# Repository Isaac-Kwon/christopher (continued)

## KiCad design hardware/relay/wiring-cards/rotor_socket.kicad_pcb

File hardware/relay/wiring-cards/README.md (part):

# 릴레이 배선 카드: 로터 카드 W와 반사판 카드 U (Phase 3 R 트랙, 회로도 + 기판 배치)

작성일: 2026-11-15 (8절 카트리지 방식 2026-11-16) · 상태: **회로도(KiCad 10) 생성·ERC 0건, 유닛 전체 넷리스트 합성·시뮬레이션·음성 시험 통과, 기판 배치(배선 없음) DRC 0건. 관람객용 카트리지 방식(받침 기판 + 카트리지 8종)도 같은 단계** · 관련: `hardware/relay/layout.md` 3.2·3.4절(카드 순서와 점퍼), `hardware/relay/concept.md`, `hardware/relay/shifter-board/README.md`(틀과 J1–J4 자리), `docs/decisions/0003-interfaces.md`(26선 D-sub, 27–29번, `CHASSIS`), 기준 모델 `crates/christopher-core/src/relay.rs`

**표기.** **(계산)** = 이 문서의 산술, **(추정)** = 시제품 전 값. 단위 mm.

## 1. 무엇인가

릴레이 유닛(`S(a1) W_R S(a2) W_M S(a3) W_L S(−l) + 반사판 + 같은 보드를 거꾸로`)에서 시프터가 아닌 **수동 배선 카드** 두 종류.

| 카드 | 종류 | 내용 | 프로젝트 |
|---|---|---|---|
| **W** (로터) | 8종 (로터 I–VIII 하나씩) | 가는 길 `i → W[i]`, 오는 길 `W[i] → i` (= W⁻¹). 커넥터 4개(J1–J4), 부품은 커넥터와 장착 구멍뿐 | `rotor_I` … `rotor_VIII` |
| **U** (반사판) | 2종 (B, C. 얇은 반사판은 불필요) | 가는 길 `i → R[i]`로 되돌림. 커넥터 2개(J2, J3) | `reflector_B`, `reflector_C` |

배선은 `data/wirings/enigma.txt`에서 생성한다(단일 출처). 카드는 **시프터와 같은 외곽 250 × 228, 같은 구멍 4개, 같은 D-sub 37 풋프린트를 시프터의 J1–J4와 같은 좌표·방향에** 둔다. 층은 2층(수동이라 충분, 4층으로 바꿔도 배치는 같다).

| 파일 | 내용 |
|---|---|
| `gen_cards.py` | 열 개 프로젝트(`.kicad_pro`, `.kicad_sch`)를 생성. 회로도는 평면 한 장(A3) |
| `gen_cards_pcb.py` | 기판 배치 생성(외곽, 구멍, 커넥터, 넷리스트, 실크). 배선 없음 |
| `verify_cards.py` | **유닛 전체 넷리스트 합성 + 스크램블러와의 비교 + 음성 시험**(4절) |
| `verify_cards_pcb.py` | 배치 대 회로도, DRC, 시프터와 같은 자리, 결정성, 음성 시험(5절) |
| `ki_common.py` | KiCad 보조 모듈. `hardware/gear/contact-board/ki_common.py`와 **같은 사본** |

생성물은 UUID를 고정해 두어 다시 생성해도 바이트 단위로 같다. 손으로 고치지 말고 생성기를 고친다.

## 2. 규약: 쌓기의 방향 (명시)

**커넥터 이름은 시프터의 J1–J4 자리 이름이고 신호의 방향이 아니다.** 시프터는 J1(가는 길 입력)·J2(오는 길 입력)가 한 변, J3(가는 길 출력)·J4(오는 길 출력)가 맞은편 변이다. 로터 카드와 반사판 카드는 같은 자리에 같은 이름을 쓰되 기능이 다르다.

| 카드 | 커넥터 (자리) | 기능 | 쌓기에서의 변·자리 |
|---|---|---|---|
| W | **J3** (오른쪽 변 h1) | `OUTBOUND_IN` 가는 길 입력 | 아래 h1 |
| W | **J4** (오른쪽 변 h2) | `RETURN_IN` 오는 길 입력 | 아래 h2 |
| W | **J1** (왼쪽 변 h1) | `OUTBOUND_OUT` 가는 길 출력 | 위 h1 |
| W | **J2** (왼쪽 변 h2) | `RETURN_OUT` 오는 길 출력 | 위 h2 |
| U | **J3** | `OUTBOUND_IN` (S4의 가는 길 출구에서 받음) | 아래 h1 |
| U | **J2** | `RETURN_OUT` (S4의 오는 길 입구로 보냄) | 위 h2 |

- **왜 W의 입력이 J3·J4인가.** layout.md 3.2절: S1–S3와 W와 U는 부품면이 **뒤**를 보고, 연결 변이 위와 아래다. 뒤를 보는 카드는 J3·J4 변이 **아래**, J1·J2 변이 **위**다(시프터 S1–S3 표). 신호는 S1에서 S4 쪽으로 가므로 W의 입력은 앞 시프터 S(k)의 **출력 변(J3·J4, 아래)**에서 받고, 출력은 다음 시프터의 **입력 변(J1·J2, 위)**으로 나간다. 그래서 W 입력이 J3·J4(아래), 출력이 J1·J2(위)다. 결과로 **같은 자리의 커넥터끼리 곧게 잇는** 규칙(`S1.J3 – W_R.J3`, `W_R.J1 – S2.J1`, …)이 성립한다.
- **a4(앞을 보는 S4)**는 J1·J2가 아래, J3·J4가 위다. S4는 시프터 기판의 **S4 변형**(`shifter_board_s4.kicad_pcb`, 7절 1번)이다: 신호 배정과 변·자리는 표준과 같고 J1–J4가 뒷면에 거울로 놓여 점퍼 14가닥 모두 양 끝 소켓의 핀 1이 같은 끝에 온다. 가는 길은 위의 J3으로 들어가 아래의 J1로 나온다(`−l`).
- 카드가 쌓기에서 도는 방식(앞 보기/뒤 보기, 변과 자리)은 `verify_cards.py`의 `POSE` 표에 있고, **점퍼 14가닥은 이 표에서 도출한다**: 변·자리마다 앞에서 뒤 순서로 커넥터를 두 개씩 짝지으면 layout.md 3.4절의 표와 정확히 같다(길이 39 ×2, 64 ×2, 25 ×10도 같음). 짝이 없는 끝이 `IN`(S1.J1)·`OUT`(S1.J4) 리드다.

점퍼(핀 n = 핀 n, 37선 1:1):

| 변·자리 | 점퍼 |
|---|---|
| 아래 h1 | S4.J1 – U.J3 · W_L.J3 – S3.J3 · W_M.J3 – S2.J3 · W_R.J3 – S1.J3 |
| 아래 h2 | S4.J2 – W_L.J4 · S3.J4 – W_M.J4 · S2.J4 – W_R.J4 · S1.J4 → `OUT` 리드 |
| 위 h1 | S4.J3 – W_L.J1 · S3.J1 – W_M.J1 · S2.J1 – W_R.J1 · `IN` 리드 → S1.J1 |
| 위 h2 | S4.J4 – U.J2 · W_L.J2 – S3.J2 · W_M.J2 – S2.J2 · W_R.J2 – S1.J2 |

전류의 길: `IN` → S1 → **W_R(J3→J1)** → S2 → W_M → S3 → W_L → S4(J3→J1) → **U(J3→J2)** → S4(J4→J2) → **W_L(J4→J2)** → S3 → W_M → S2 → W_R → S1 → `OUT`.

## 3. 카드의 회로

**W 카드 (로터 N).** 핀 1–26 = 선 A–Z. 가는 길: **J3 핀 i+1 → J1 핀 W[i]+1** (네트 `OW_<입력><출력>`, 예: 로터 I `OW_AE`). 오는 길: **J4 핀 j+1 → J2 핀 W⁻¹[j]+1** (네트 `RW_<입력><출력>`). 즉 오는 길은 같은 와이어링을 거꾸로 읽는다(`relay.rs`의 `backward`). 로터 한 장에 2-핀 네트 52개. W[i]는 enigma.txt의 "입구쪽 → 반사판쪽" 표(코어 오프셋 0)이고, 로터의 회전은 시프터 쪽(`a1…a4`)이 한다. 카드에는 이동 위치·노치가 없다.

**U 카드 (반사판 N).** **J3 핀 i+1 ↔ J2 핀 R[i]+1** (네트 `RF_<입력><출력>`, 26개). 반사판은 고정점 없는 대합(R[R[i]] = i)이므로 카드를 끝에서 끝으로 돌려 꽂아도(J3↔J2) 같은 배선이다(7절 2번).

**공통.** 핀 27–29(0 V 기준선, 0003 5.2절)와 30–37은 어디에도 잇지 않는다(`no_connect`, 점퍼의 27–37 가닥은 양쪽 모두 떠 있다). D-sub 껍데기(풋프린트 패드 `SH`, 커넥터마다 2개)와 장착 구멍 H1–H4(도금 M3)는 `CHASSIS`(0003 7.1절). 이 카드에는 0 V도 전원도 없으므로 `CHASSIS`–0 V의 R6·C1은 시프터에만 있다(`CHASSIS` 넷에 PWR_FLAG 하나, ERC용).

## 4. 유닛 전체 검증 (`verify_cards.py`)

`python verify_cards.py [--samples 50] [--exhaustive "B II IV V" | all] [--quick]` (KiCad 10, christopher 패키지가 든 venv).

합성은 **실제 생성된 넷리스트**로 한다(kicad-cli로 내보낸 `shifter_board`, `rotor_*`, `reflector_*`):

- 시프터 보드 4장 S1–S4(릴레이 130개씩), W 카드 3장(고른 휠 순서), U 카드 1장, 2절의 점퍼 14가닥(핀 n = 핀 n). a4는 점퍼가 만드는 방향(J3로 들어가 J1로 나감)으로 거꾸로 쓴다. 점퍼는 카드 자세 표에서 **도출**하고 layout.md 표와 같은지 확인한다.
- 시프터 단 릴레이는 `Controls::from_cores`의 파이썬 이식으로 설정한다(`a1 = r + k`, `a2 = m − a1`, `a3 = l − m`, S4의 제어 `a4 = l`). 접점은 G6S-2 핀 기능(`verify_shifter.py`와 같음), 연결은 넷 + 닫힌 접점 + 점퍼의 합집합-찾기.
- 각 위치에서 `IN`(S1.J1 핀 i)이 **정확히 `OUT`(S1.J4 핀 s(i))에만** 이어지고(26선 모두, 선끼리·제어 핀과 단락 없음) s가 Enigma 스크램블러와 같음을 확인한다. 기준: christopher의 `Bombe.trace`(한 변 메뉴 A→B, 입력선 w의 출력 = 스크램블러(w), `diagonal_board=False`). `WheelOrder::scrambler`의 파이썬 이식은 같은 위치에서 trace와 교차 확인(불일치 0).
- 카드 단위 검사: 각 W 카드가 enigma.txt의 W와 W⁻¹과 같고(핀 단위, 다른 연결 없음), U가 R과 같고, 27–37이 뜨고, `CHASSIS`가 H1–H4뿐.

**결과**(2026-11-15, 전부 통과; 시간은 이 PC에서 약 30초):

| 범위 | 규모 | 결과 |
|---|---|---|
| 카드 넷리스트 대 enigma.txt | W 8종, U 2종 | 일치 |
| 점퍼 도출 | 14가닥 + 리드 2, 길이 25 ×12 / 50 ×2(S4 변형은 소켓이 뒷면) | layout.md 3.4절과 일치 |
| 핀 1 정렬(기판 파일의 풋프린트 자세) | 점퍼 14가닥 + 리드 2 | 14/14, 리드 2/2 일치 |
| Enigma I 60개 휠 순서, 반사판 B | 순서당 50위치(모서리 2 + 임의 48, 3분의 1은 임의 k) = 3,000위치 × 26선 | 모두 일치 |
| I–VIII 3-로터 전체 순서, 반사판 B와 C | 336 × 2 = 672 순서 × 4위치 = 2,688위치 | 모두 일치(VI–VIII 카드와 반사판 C 포함) |
| 한 순서 전수 `B II IV V` | 17,576위치 × 26선 | 모두 일치 |
| 전수 `--exhaustive all` | Enigma I 60개 순서 전부 × 17,576위치 | 모두 일치(60 × 17,576 = 1,054,560위치 × 26선, 약 13분, 파이썬 이식과 trace 불일치 0) |

**음성 시험**(변형한 유닛이 의도한 순서의 스크램블러와 달라져야 함, 17건 모두 검출; 핀 1 시험 3건 포함: **표준 시프터를 S4로 쓰는 옛 구성 = 4가닥 어긋남**, S1–S3에도 S4 변형을 씀, W.J1의 핀 1 끝을 바꿈): W_M–S2 점퍼의 두 가닥 맞바꿈, W_M의 가는 길·오는 길 점퍼를 서로의 커넥터에 꽂음, W_M을 끝에서 끝으로 돌려 꽂음(W와 W⁻¹ 교환), S4–U 점퍼의 두 가닥 맞바꿈, **a4를 S1–S3처럼 꽂음(거꾸로 아님)**, 잘못된 카드(W_M = IV, W_L ↔ W_M), **잘못된 반사판(C)**, S4 점퍼를 엉뚱한 커넥터에 꽂음, S4를 뒤 보기로 하면 점퍼 표가 layout.md와 달라짐, 카드 넷리스트에서 핀 두 개 맞바꿈 4건(W J1·J2·J3, U J2: 유닛 시뮬레이션과 카드 검사가 모두 잡음).

## 5. 기판 배치 (`gen_cards_pcb.py`, `verify_cards_pcb.py`)

범위: 외곽, 장착 구멍, 커넥터, 넷리스트(래츠넷), 실크. **배선·비아·존 없음**(사용자가 나중에 함).

- 외곽 250 × 228, 모서리 구멍 4개(5 mm 안쪽, 도금 M3, `CHASSIS`)는 시프터와 같다. 커넥터는 J1·J2 왼쪽 변(회전 270), J3·J4 오른쪽 변(회전 90), 좌표 = 시프터의 값(`J1 (12.74, 22.28)`, `J2 (12.74, 96.29)`, `J3 (237.26, 72.13)`, `J4 (237.26, 146.14)`). U는 J2·J3만 둔다.
- 실크(부품면): 카드 이름, A–Z와 와이어링, 쌓기 방향(부품면이 뒤, IN 변 = 아래 J3·J4, OUT 변 = 위 J1·J2), 커넥터 기능.
- 2층, 설계 규칙은 시프터와 같은 저가 업체 표준(선폭/간격 0.15, 비아 0.5/0.25).

**결과**(`verify_cards_pcb.py`, PASS): 10장 모두 회로도 부품·풋프린트·IPC-D-356 패드 넷이 회로도와 같음(껍데기 패드는 `CHASSIS`), DRC(모든 심각도) **위반 0건**, 연결 안 됨 = 래츠넷(W 63 = 52 + `CHASSIS` 11, U 33 = 26 + 7; pcbnew 개수와 일치), 커넥터·구멍·외곽이 `shifter_board.kicad_pcb`와 좌표·회전·풋프린트까지 같음, 회로도·기판 재생성이 바이트 단위로 같음. 음성 시험 3건(패드 넷 맞바꿈, 커넥터 1 mm 이동, 외곽 1 mm) 검출. 점퍼 14가닥과 리드의 **핀 1 정렬**을 풋프린트 자세에서 검사한다(S4는 `shifter_board_s4.kicad_pcb`; 전부 일치, 표준 시프터를 S4로 쓰면 4가닥 어긋남이 정보로 출력됨).

재생성: `python gen_cards.py && python gen_cards_pcb.py && python verify_cards.py && python verify_cards_pcb.py`. 보고서 그림은 `report/figures/make_schematic_figures.py`, `make_pcb_figures.py`(이 폴더의 카드 열 장이 목록에 있음).

## 6. 이 폴더가 확정한 것 (layout.md의 열린 질문에 대한 답)

- W·U 카드는 시프터의 외곽과 J1–J4 자리를 그대로 쓰되 W는 입력이 J3·J4, 출력이 J1·J2다(2절). layout.md 3.2절 표의 "W: 가는 길 입력(h1)…" 은 이 이름에 대응한다.
- U는 커넥터 둘(J3 = 가는 길 입력, J2 = 오는 길 출력)이면 된다.
- 로터 카드는 슬롯(W_L·W_M·W_R)에 무관하게 같은 카드다(슬롯마다 점퍼만 다름). 카드를 바꿔 끼워도 시프터 제어값은 그대로이며 휠 순서는 카드 선택으로만 정해진다.

## 7. 열린 질문

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
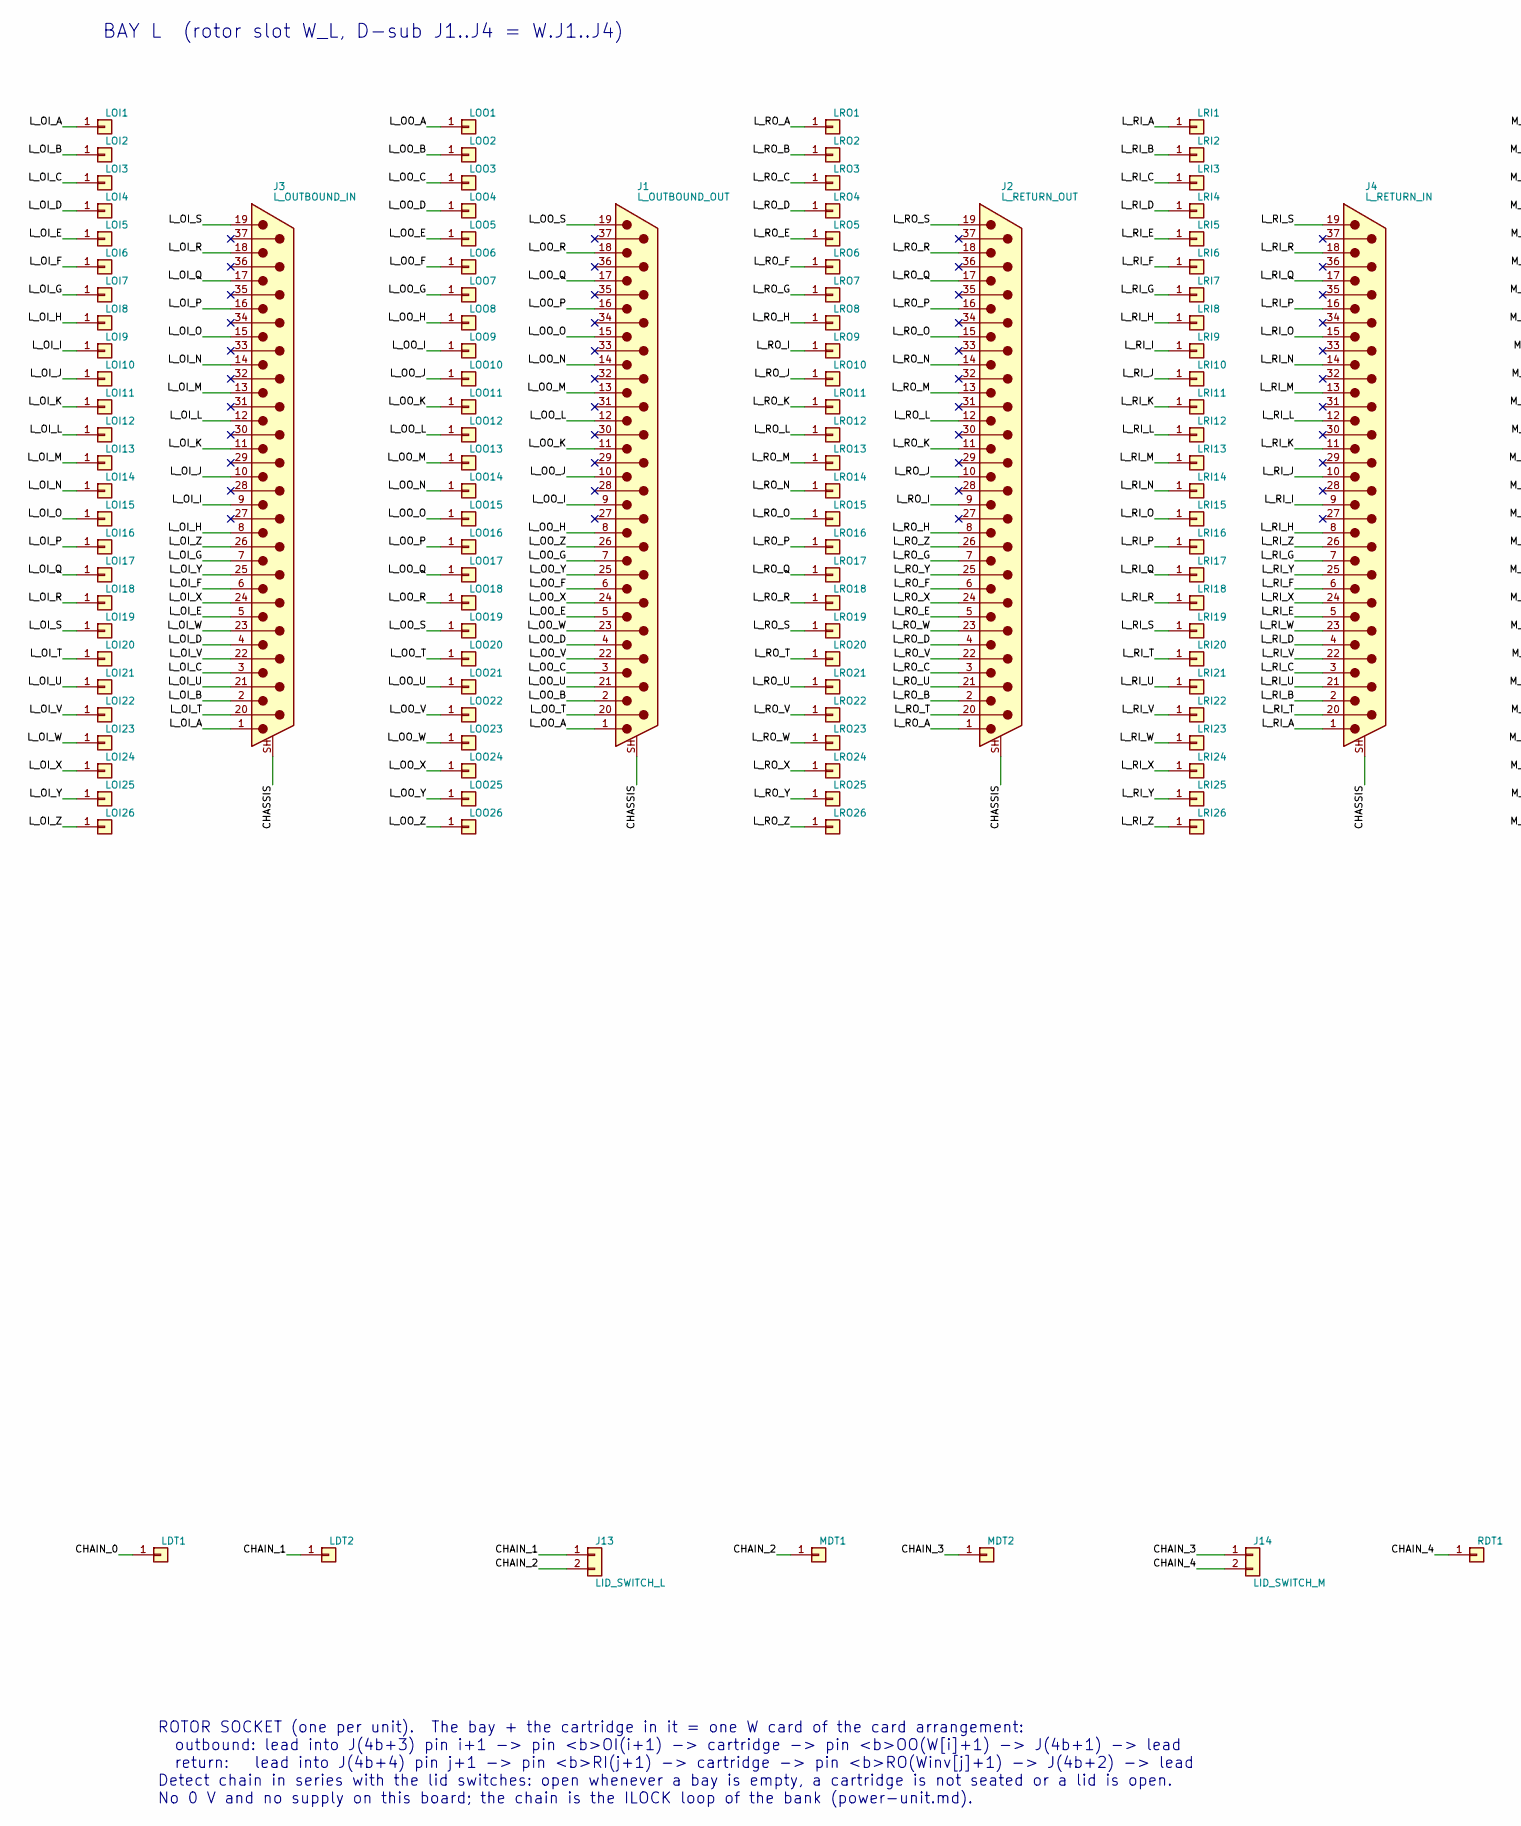
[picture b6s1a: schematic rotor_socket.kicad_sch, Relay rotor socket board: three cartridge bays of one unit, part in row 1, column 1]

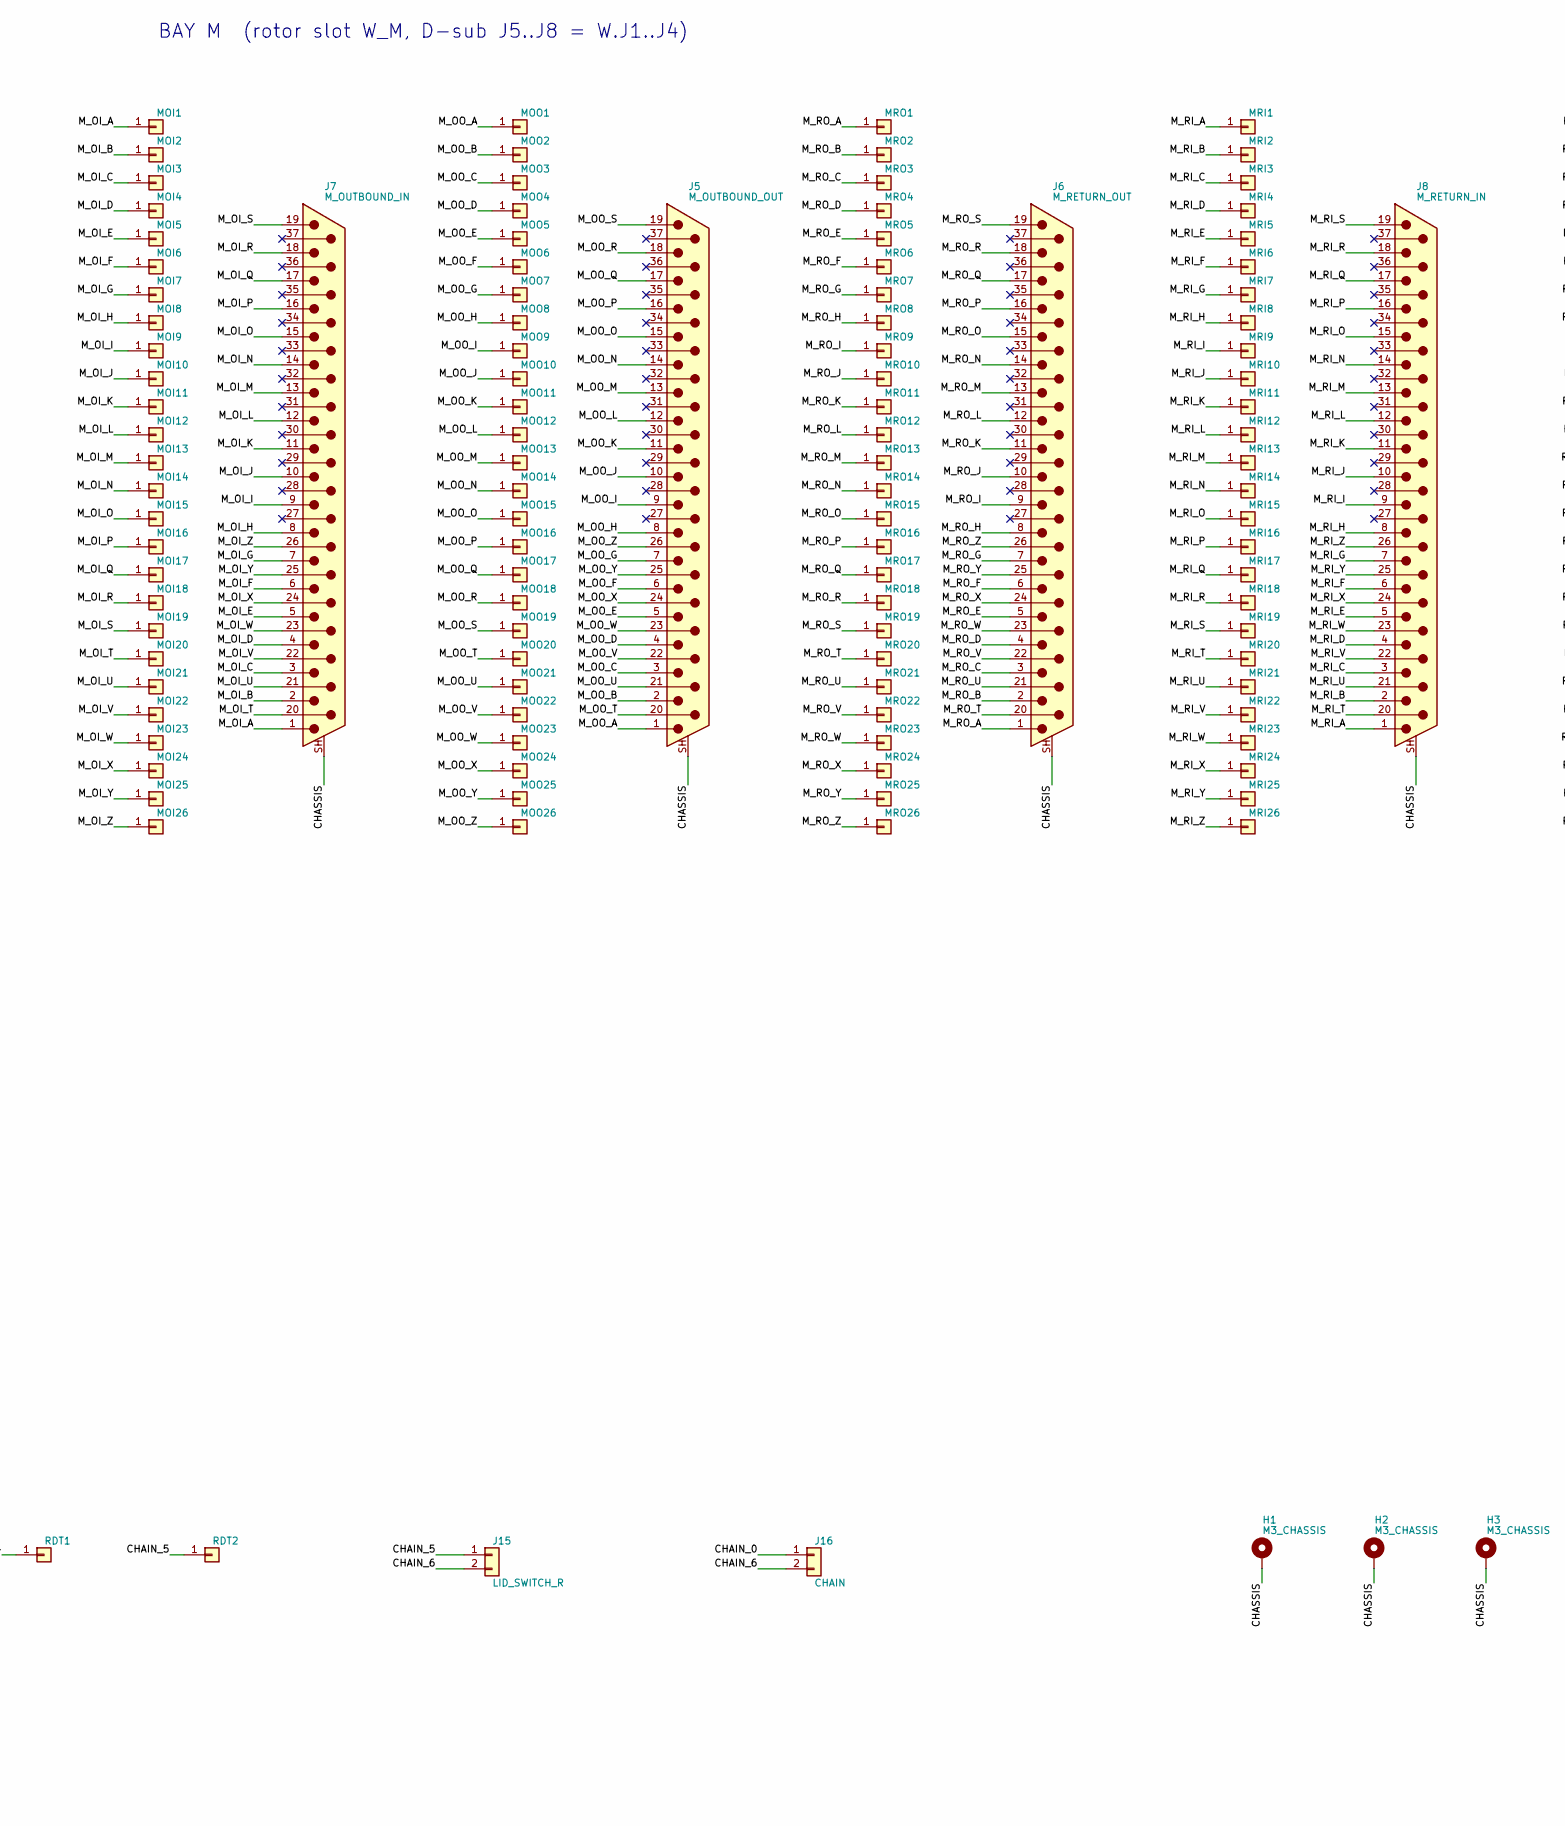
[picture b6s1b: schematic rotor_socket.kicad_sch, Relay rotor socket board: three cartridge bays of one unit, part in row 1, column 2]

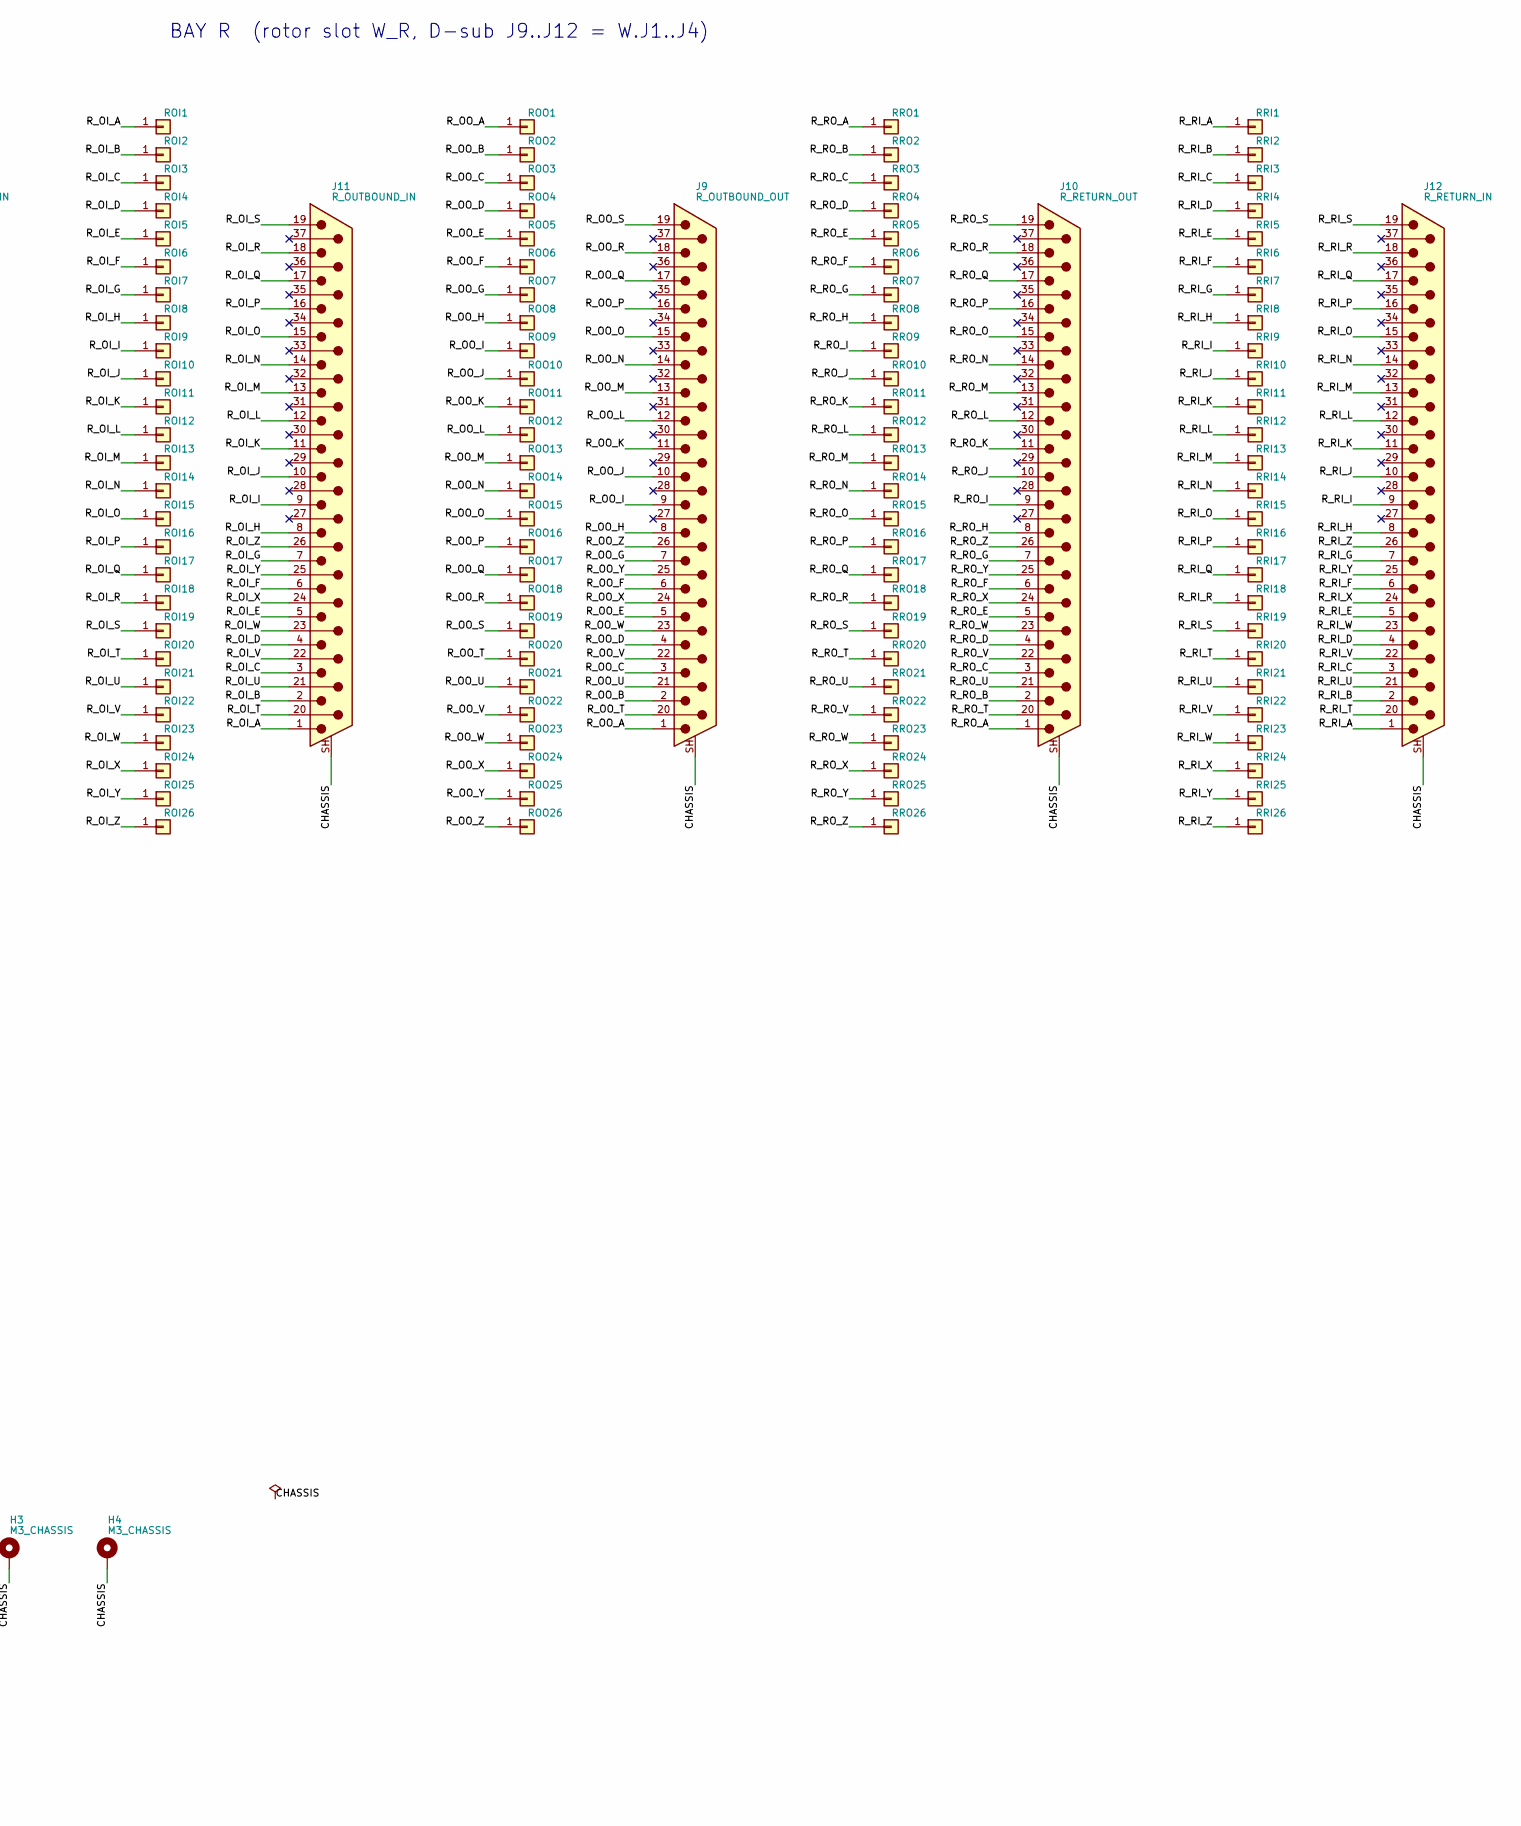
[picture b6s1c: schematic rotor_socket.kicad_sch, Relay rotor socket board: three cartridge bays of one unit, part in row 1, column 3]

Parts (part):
H1, H2, H3, H4: M3_CHASSIS; MountingHole_3.2mm_M3_Pad
J1: L_OUTBOUND_OUT; DSUB-37_Pins_Vertical_P2.77x2.84mm_MountingHoles
J2: L_RETURN_OUT; DSUB-37_Pins_Vertical_P2.77x2.84mm_MountingHoles
J3: L_OUTBOUND_IN; DSUB-37_Pins_Vertical_P2.77x2.84mm_MountingHoles
J4: L_RETURN_IN; DSUB-37_Pins_Vertical_P2.77x2.84mm_MountingHoles
J5: M_OUTBOUND_OUT; DSUB-37_Pins_Vertical_P2.77x2.84mm_MountingHoles
J6: M_RETURN_OUT; DSUB-37_Pins_Vertical_P2.77x2.84mm_MountingHoles
J7: M_OUTBOUND_IN; DSUB-37_Pins_Vertical_P2.77x2.84mm_MountingHoles
J8: M_RETURN_IN; DSUB-37_Pins_Vertical_P2.77x2.84mm_MountingHoles
J9: R_OUTBOUND_OUT; DSUB-37_Pins_Vertical_P2.77x2.84mm_MountingHoles
J10: R_RETURN_OUT; DSUB-37_Pins_Vertical_P2.77x2.84mm_MountingHoles
J11: R_OUTBOUND_IN; DSUB-37_Pins_Vertical_P2.77x2.84mm_MountingHoles
J12: R_RETURN_IN; DSUB-37_Pins_Vertical_P2.77x2.84mm_MountingHoles
J13: LID_SWITCH_L; JST_XH_B2B-XH-A_1x02_P2.50mm_Vertical
J14: LID_SWITCH_M; JST_XH_B2B-XH-A_1x02_P2.50mm_Vertical
J15: LID_SWITCH_R; JST_XH_B2B-XH-A_1x02_P2.50mm_Vertical
J16: CHAIN; JST_XH_B2B-XH-A_1x02_P2.50mm_Vertical
LDT1: DETECT L1; SpringPin_SMD_D1.6_P2.54
LDT2: DETECT L2; SpringPin_SMD_D1.6_P2.54
LOI1: PIN L OI A; SpringPin_SMD_D1.6_P2.54
LOI2: PIN L OI B; SpringPin_SMD_D1.6_P2.54
LOI3: PIN L OI C; SpringPin_SMD_D1.6_P2.54
LOI4: PIN L OI D; SpringPin_SMD_D1.6_P2.54
LOI5: PIN L OI E; SpringPin_SMD_D1.6_P2.54
LOI6: PIN L OI F; SpringPin_SMD_D1.6_P2.54
LOI7: PIN L OI G; SpringPin_SMD_D1.6_P2.54
LOI8: PIN L OI H; SpringPin_SMD_D1.6_P2.54
LOI9: PIN L OI I; SpringPin_SMD_D1.6_P2.54
LOI10: PIN L OI J; SpringPin_SMD_D1.6_P2.54
LOI11: PIN L OI K; SpringPin_SMD_D1.6_P2.54
LOI12: PIN L OI L; SpringPin_SMD_D1.6_P2.54
LOI13: PIN L OI M; SpringPin_SMD_D1.6_P2.54
LOI14: PIN L OI N; SpringPin_SMD_D1.6_P2.54
LOI15: PIN L OI O; SpringPin_SMD_D1.6_P2.54
LOI16: PIN L OI P; SpringPin_SMD_D1.6_P2.54
LOI17: PIN L OI Q; SpringPin_SMD_D1.6_P2.54
LOI18: PIN L OI R; SpringPin_SMD_D1.6_P2.54
LOI19: PIN L OI S; SpringPin_SMD_D1.6_P2.54
LOI20: PIN L OI T; SpringPin_SMD_D1.6_P2.54
LOI21: PIN L OI U; SpringPin_SMD_D1.6_P2.54
LOI22: PIN L OI V; SpringPin_SMD_D1.6_P2.54
LOI23: PIN L OI W; SpringPin_SMD_D1.6_P2.54
LOI24: PIN L OI X; SpringPin_SMD_D1.6_P2.54
LOI25: PIN L OI Y; SpringPin_SMD_D1.6_P2.54
LOI26: PIN L OI Z; SpringPin_SMD_D1.6_P2.54
LOO1: PIN L OO A; SpringPin_SMD_D1.6_P2.54
LOO2: PIN L OO B; SpringPin_SMD_D1.6_P2.54
LOO3: PIN L OO C; SpringPin_SMD_D1.6_P2.54
LOO4: PIN L OO D; SpringPin_SMD_D1.6_P2.54
LOO5: PIN L OO E; SpringPin_SMD_D1.6_P2.54
LOO6: PIN L OO F; SpringPin_SMD_D1.6_P2.54
LOO7: PIN L OO G; SpringPin_SMD_D1.6_P2.54
LOO8: PIN L OO H; SpringPin_SMD_D1.6_P2.54
LOO9: PIN L OO I; SpringPin_SMD_D1.6_P2.54
LOO10: PIN L OO J; SpringPin_SMD_D1.6_P2.54
LOO11: PIN L OO K; SpringPin_SMD_D1.6_P2.54
LOO12: PIN L OO L; SpringPin_SMD_D1.6_P2.54
LOO13: PIN L OO M; SpringPin_SMD_D1.6_P2.54
LOO14: PIN L OO N; SpringPin_SMD_D1.6_P2.54
LOO15: PIN L OO O; SpringPin_SMD_D1.6_P2.54
LOO16: PIN L OO P; SpringPin_SMD_D1.6_P2.54
LOO17: PIN L OO Q; SpringPin_SMD_D1.6_P2.54
LOO18: PIN L OO R; SpringPin_SMD_D1.6_P2.54
LOO19: PIN L OO S; SpringPin_SMD_D1.6_P2.54
LOO20: PIN L OO T; SpringPin_SMD_D1.6_P2.54
LOO21: PIN L OO U; SpringPin_SMD_D1.6_P2.54
LOO22: PIN L OO V; SpringPin_SMD_D1.6_P2.54
LOO23: PIN L OO W; SpringPin_SMD_D1.6_P2.54
LOO24: PIN L OO X; SpringPin_SMD_D1.6_P2.54
LOO25: PIN L OO Y; SpringPin_SMD_D1.6_P2.54
LOO26: PIN L OO Z; SpringPin_SMD_D1.6_P2.54
LRI1: PIN L RI A; SpringPin_SMD_D1.6_P2.54
LRI2: PIN L RI B; SpringPin_SMD_D1.6_P2.54
LRI3: PIN L RI C; SpringPin_SMD_D1.6_P2.54
LRI4: PIN L RI D; SpringPin_SMD_D1.6_P2.54
LRI5: PIN L RI E; SpringPin_SMD_D1.6_P2.54
LRI6: PIN L RI F; SpringPin_SMD_D1.6_P2.54
LRI7: PIN L RI G; SpringPin_SMD_D1.6_P2.54
LRI8: PIN L RI H; SpringPin_SMD_D1.6_P2.54
LRI9: PIN L RI I; SpringPin_SMD_D1.6_P2.54
LRI10: PIN L RI J; SpringPin_SMD_D1.6_P2.54
LRI11: PIN L RI K; SpringPin_SMD_D1.6_P2.54
LRI12: PIN L RI L; SpringPin_SMD_D1.6_P2.54
LRI13: PIN L RI M; SpringPin_SMD_D1.6_P2.54
LRI14: PIN L RI N; SpringPin_SMD_D1.6_P2.54
LRI15: PIN L RI O; SpringPin_SMD_D1.6_P2.54
LRI16: PIN L RI P; SpringPin_SMD_D1.6_P2.54
LRI17: PIN L RI Q; SpringPin_SMD_D1.6_P2.54
LRI18: PIN L RI R; SpringPin_SMD_D1.6_P2.54
LRI19: PIN L RI S; SpringPin_SMD_D1.6_P2.54
LRI20: PIN L RI T; SpringPin_SMD_D1.6_P2.54
LRI21: PIN L RI U; SpringPin_SMD_D1.6_P2.54
LRI22: PIN L RI V; SpringPin_SMD_D1.6_P2.54
LRI23: PIN L RI W; SpringPin_SMD_D1.6_P2.54
LRI24: PIN L RI X; SpringPin_SMD_D1.6_P2.54
LRI25: PIN L RI Y; SpringPin_SMD_D1.6_P2.54
LRI26: PIN L RI Z; SpringPin_SMD_D1.6_P2.54
LRO1: PIN L RO A; SpringPin_SMD_D1.6_P2.54
LRO2: PIN L RO B; SpringPin_SMD_D1.6_P2.54
LRO3: PIN L RO C; SpringPin_SMD_D1.6_P2.54
LRO4: PIN L RO D; SpringPin_SMD_D1.6_P2.54
LRO5: PIN L RO E; SpringPin_SMD_D1.6_P2.54
LRO6: PIN L RO F; SpringPin_SMD_D1.6_P2.54
LRO7: PIN L RO G; SpringPin_SMD_D1.6_P2.54
LRO8: PIN L RO H; SpringPin_SMD_D1.6_P2.54
LRO9: PIN L RO I; SpringPin_SMD_D1.6_P2.54
LRO10: PIN L RO J; SpringPin_SMD_D1.6_P2.54
LRO11: PIN L RO K; SpringPin_SMD_D1.6_P2.54
LRO12: PIN L RO L; SpringPin_SMD_D1.6_P2.54
LRO13: PIN L RO M; SpringPin_SMD_D1.6_P2.54
LRO14: PIN L RO N; SpringPin_SMD_D1.6_P2.54
LRO15: PIN L RO O; SpringPin_SMD_D1.6_P2.54
LRO16: PIN L RO P; SpringPin_SMD_D1.6_P2.54
LRO17: PIN L RO Q; SpringPin_SMD_D1.6_P2.54
LRO18: PIN L RO R; SpringPin_SMD_D1.6_P2.54
LRO19: PIN L RO S; SpringPin_SMD_D1.6_P2.54
LRO20: PIN L RO T; SpringPin_SMD_D1.6_P2.54
LRO21: PIN L RO U; SpringPin_SMD_D1.6_P2.54
LRO22: PIN L RO V; SpringPin_SMD_D1.6_P2.54
LRO23: PIN L RO W; SpringPin_SMD_D1.6_P2.54
LRO24: PIN L RO X; SpringPin_SMD_D1.6_P2.54
LRO25: PIN L RO Y; SpringPin_SMD_D1.6_P2.54
LRO26: PIN L RO Z; SpringPin_SMD_D1.6_P2.54
MDT1: DETECT M1; SpringPin_SMD_D1.6_P2.54
MDT2: DETECT M2; SpringPin_SMD_D1.6_P2.54
MOI1: PIN M OI A; SpringPin_SMD_D1.6_P2.54
MOI2: PIN M OI B; SpringPin_SMD_D1.6_P2.54
MOI3: PIN M OI C; SpringPin_SMD_D1.6_P2.54
MOI4: PIN M OI D; SpringPin_SMD_D1.6_P2.54
MOI5: PIN M OI E; SpringPin_SMD_D1.6_P2.54
MOI6: PIN M OI F; SpringPin_SMD_D1.6_P2.54
MOI7: PIN M OI G; SpringPin_SMD_D1.6_P2.54
MOI8: PIN M OI H; SpringPin_SMD_D1.6_P2.54
MOI9: PIN M OI I; SpringPin_SMD_D1.6_P2.54
MOI10: PIN M OI J; SpringPin_SMD_D1.6_P2.54
MOI11: PIN M OI K; SpringPin_SMD_D1.6_P2.54
MOI12: PIN M OI L; SpringPin_SMD_D1.6_P2.54
MOI13: PIN M OI M; SpringPin_SMD_D1.6_P2.54
MOI14: PIN M OI N; SpringPin_SMD_D1.6_P2.54
MOI15: PIN M OI O; SpringPin_SMD_D1.6_P2.54
MOI16: PIN M OI P; SpringPin_SMD_D1.6_P2.54
MOI17: PIN M OI Q; SpringPin_SMD_D1.6_P2.54
MOI18: PIN M OI R; SpringPin_SMD_D1.6_P2.54
MOI19: PIN M OI S; SpringPin_SMD_D1.6_P2.54
MOI20: PIN M OI T; SpringPin_SMD_D1.6_P2.54
MOI21: PIN M OI U; SpringPin_SMD_D1.6_P2.54
MOI22: PIN M OI V; SpringPin_SMD_D1.6_P2.54
MOI23: PIN M OI W; SpringPin_SMD_D1.6_P2.54
MOI24: PIN M OI X; SpringPin_SMD_D1.6_P2.54
MOI25: PIN M OI Y; SpringPin_SMD_D1.6_P2.54
MOI26: PIN M OI Z; SpringPin_SMD_D1.6_P2.54
MOO1: PIN M OO A; SpringPin_SMD_D1.6_P2.54
MOO2: PIN M OO B; SpringPin_SMD_D1.6_P2.54
MOO3: PIN M OO C; SpringPin_SMD_D1.6_P2.54
MOO4: PIN M OO D; SpringPin_SMD_D1.6_P2.54
MOO5: PIN M OO E; SpringPin_SMD_D1.6_P2.54
MOO6: PIN M OO F; SpringPin_SMD_D1.6_P2.54
MOO7: PIN M OO G; SpringPin_SMD_D1.6_P2.54
MOO8: PIN M OO H; SpringPin_SMD_D1.6_P2.54
MOO9: PIN M OO I; SpringPin_SMD_D1.6_P2.54
MOO10: PIN M OO J; SpringPin_SMD_D1.6_P2.54
MOO11: PIN M OO K; SpringPin_SMD_D1.6_P2.54
MOO12: PIN M OO L; SpringPin_SMD_D1.6_P2.54
MOO13: PIN M OO M; SpringPin_SMD_D1.6_P2.54
MOO14: PIN M OO N; SpringPin_SMD_D1.6_P2.54
MOO15: PIN M OO O; SpringPin_SMD_D1.6_P2.54
MOO16: PIN M OO P; SpringPin_SMD_D1.6_P2.54
MOO17: PIN M OO Q; SpringPin_SMD_D1.6_P2.54
MOO18: PIN M OO R; SpringPin_SMD_D1.6_P2.54
MOO19: PIN M OO S; SpringPin_SMD_D1.6_P2.54
MOO20: PIN M OO T; SpringPin_SMD_D1.6_P2.54
MOO21: PIN M OO U; SpringPin_SMD_D1.6_P2.54
MOO22: PIN M OO V; SpringPin_SMD_D1.6_P2.54
MOO23: PIN M OO W; SpringPin_SMD_D1.6_P2.54
MOO24: PIN M OO X; SpringPin_SMD_D1.6_P2.54
MOO25: PIN M OO Y; SpringPin_SMD_D1.6_P2.54
MOO26: PIN M OO Z; SpringPin_SMD_D1.6_P2.54
MRI1: PIN M RI A; SpringPin_SMD_D1.6_P2.54
MRI2: PIN M RI B; SpringPin_SMD_D1.6_P2.54
MRI3: PIN M RI C; SpringPin_SMD_D1.6_P2.54
MRI4: PIN M RI D; SpringPin_SMD_D1.6_P2.54
MRI5: PIN M RI E; SpringPin_SMD_D1.6_P2.54
MRI6: PIN M RI F; SpringPin_SMD_D1.6_P2.54
MRI7: PIN M RI G; SpringPin_SMD_D1.6_P2.54
MRI8: PIN M RI H; SpringPin_SMD_D1.6_P2.54
MRI9: PIN M RI I; SpringPin_SMD_D1.6_P2.54
MRI10: PIN M RI J; SpringPin_SMD_D1.6_P2.54
MRI11: PIN M RI K; SpringPin_SMD_D1.6_P2.54
MRI12: PIN M RI L; SpringPin_SMD_D1.6_P2.54
MRI13: PIN M RI M; SpringPin_SMD_D1.6_P2.54
MRI14: PIN M RI N; SpringPin_SMD_D1.6_P2.54
MRI15: PIN M RI O; SpringPin_SMD_D1.6_P2.54
MRI16: PIN M RI P; SpringPin_SMD_D1.6_P2.54
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
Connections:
/CHAIN_0: J16.1, LDT1.1
/CHAIN_1: J13.1, LDT2.1
/CHAIN_2: J13.2, MDT1.1
/CHAIN_3: J14.1, MDT2.1
/CHAIN_4: J14.2, RDT1.1
/CHAIN_5: J15.1, RDT2.1
/CHAIN_6: J15.2, J16.2
/CHASSIS: H1.1, H2.1, H3.1, H4.1, J1.SH (PAD), J2.SH (PAD), J3.SH (PAD), J4.SH (PAD), J5.SH (PAD), J6.SH (PAD), J7.SH (PAD), J8.SH (PAD), J9.SH (PAD), J10.SH (PAD), J11.SH (PAD), J12.SH (PAD)
/L_OI_A: J3.1, LOI1.1
/L_OI_B: J3.2, LOI2.1
/L_OI_C: J3.3, LOI3.1
/L_OI_D: J3.4, LOI4.1
/L_OI_E: J3.5, LOI5.1
/L_OI_F: J3.6, LOI6.1
/L_OI_G: J3.7, LOI7.1
/L_OI_H: J3.8, LOI8.1
/L_OI_I: J3.9, LOI9.1
/L_OI_J: J3.10, LOI10.1
/L_OI_K: J3.11, LOI11.1
/L_OI_L: J3.12, LOI12.1
/L_OI_M: J3.13, LOI13.1
/L_OI_N: J3.14, LOI14.1
/L_OI_O: J3.15, LOI15.1
/L_OI_P: J3.16, LOI16.1
/L_OI_Q: J3.17, LOI17.1
/L_OI_R: J3.18, LOI18.1
/L_OI_S: J3.19, LOI19.1
/L_OI_T: J3.20, LOI20.1
/L_OI_U: J3.21, LOI21.1
/L_OI_V: J3.22, LOI22.1
/L_OI_W: J3.23, LOI23.1
/L_OI_X: J3.24, LOI24.1
/L_OI_Y: J3.25, LOI25.1
/L_OI_Z: J3.26, LOI26.1
/L_OO_A: J1.1, LOO1.1
/L_OO_B: J1.2, LOO2.1
/L_OO_C: J1.3, LOO3.1
/L_OO_D: J1.4, LOO4.1
/L_OO_E: J1.5, LOO5.1
/L_OO_F: J1.6, LOO6.1
/L_OO_G: J1.7, LOO7.1
/L_OO_H: J1.8, LOO8.1
/L_OO_I: J1.9, LOO9.1
/L_OO_J: J1.10, LOO10.1
/L_OO_K: J1.11, LOO11.1
/L_OO_L: J1.12, LOO12.1
/L_OO_M: J1.13, LOO13.1
/L_OO_N: J1.14, LOO14.1
/L_OO_O: J1.15, LOO15.1
/L_OO_P: J1.16, LOO16.1
/L_OO_Q: J1.17, LOO17.1
/L_OO_R: J1.18, LOO18.1
/L_OO_S: J1.19, LOO19.1
/L_OO_T: J1.20, LOO20.1
/L_OO_U: J1.21, LOO21.1
/L_OO_V: J1.22, LOO22.1
/L_OO_W: J1.23, LOO23.1
/L_OO_X: J1.24, LOO24.1
/L_OO_Y: J1.25, LOO25.1
/L_OO_Z: J1.26, LOO26.1
/L_RI_A: J4.1, LRI1.1
/L_RI_B: J4.2, LRI2.1
/L_RI_C: J4.3, LRI3.1
/L_RI_D: J4.4, LRI4.1
/L_RI_E: J4.5, LRI5.1
/L_RI_F: J4.6, LRI6.1
/L_RI_G: J4.7, LRI7.1
/L_RI_H: J4.8, LRI8.1
/L_RI_I: J4.9, LRI9.1
/L_RI_J: J4.10, LRI10.1
/L_RI_K: J4.11, LRI11.1
/L_RI_L: J4.12, LRI12.1
/L_RI_M: J4.13, LRI13.1
/L_RI_N: J4.14, LRI14.1
/L_RI_O: J4.15, LRI15.1
/L_RI_P: J4.16, LRI16.1
/L_RI_Q: J4.17, LRI17.1
/L_RI_R: J4.18, LRI18.1
/L_RI_S: J4.19, LRI19.1
/L_RI_T: J4.20, LRI20.1
/L_RI_U: J4.21, LRI21.1
/L_RI_V: J4.22, LRI22.1
/L_RI_W: J4.23, LRI23.1
/L_RI_X: J4.24, LRI24.1
/L_RI_Y: J4.25, LRI25.1
/L_RI_Z: J4.26, LRI26.1
/L_RO_A: J2.1, LRO1.1
/L_RO_B: J2.2, LRO2.1
/L_RO_C: J2.3, LRO3.1
/L_RO_D: J2.4, LRO4.1
/L_RO_E: J2.5, LRO5.1
/L_RO_F: J2.6, LRO6.1
/L_RO_G: J2.7, LRO7.1
/L_RO_H: J2.8, LRO8.1
/L_RO_I: J2.9, LRO9.1
/L_RO_J: J2.10, LRO10.1
/L_RO_K: J2.11, LRO11.1
/L_RO_L: J2.12, LRO12.1
/L_RO_M: J2.13, LRO13.1
/L_RO_N: J2.14, LRO14.1
/L_RO_O: J2.15, LRO15.1
/L_RO_P: J2.16, LRO16.1
/L_RO_Q: J2.17, LRO17.1
/L_RO_R: J2.18, LRO18.1
/L_RO_S: J2.19, LRO19.1
/L_RO_T: J2.20, LRO20.1
/L_RO_U: J2.21, LRO21.1
/L_RO_V: J2.22, LRO22.1
/L_RO_W: J2.23, LRO23.1
/L_RO_X: J2.24, LRO24.1
/L_RO_Y: J2.25, LRO25.1
/L_RO_Z: J2.26, LRO26.1
/M_OI_A: J7.1, MOI1.1
/M_OI_B: J7.2, MOI2.1
/M_OI_C: J7.3, MOI3.1
/M_OI_D: J7.4, MOI4.1
/M_OI_E: J7.5, MOI5.1
/M_OI_F: J7.6, MOI6.1
/M_OI_G: J7.7, MOI7.1
/M_OI_H: J7.8, MOI8.1
/M_OI_I: J7.9, MOI9.1
/M_OI_J: J7.10, MOI10.1
/M_OI_K: J7.11, MOI11.1
/M_OI_L: J7.12, MOI12.1
/M_OI_M: J7.13, MOI13.1
/M_OI_N: J7.14, MOI14.1
/M_OI_O: J7.15, MOI15.1
/M_OI_P: J7.16, MOI16.1
/M_OI_Q: J7.17, MOI17.1
/M_OI_R: J7.18, MOI18.1
/M_OI_S: J7.19, MOI19.1
/M_OI_T: J7.20, MOI20.1
/M_OI_U: J7.21, MOI21.1
/M_OI_V: J7.22, MOI22.1
/M_OI_W: J7.23, MOI23.1
/M_OI_X: J7.24, MOI24.1
/M_OI_Y: J7.25, MOI25.1
/M_OI_Z: J7.26, MOI26.1
/M_OO_A: J5.1, MOO1.1
/M_OO_B: J5.2, MOO2.1
/M_OO_C: J5.3, MOO3.1
/M_OO_D: J5.4, MOO4.1
/M_OO_E: J5.5, MOO5.1
/M_OO_F: J5.6, MOO6.1
/M_OO_G: J5.7, MOO7.1
/M_OO_H: J5.8, MOO8.1
/M_OO_I: J5.9, MOO9.1
/M_OO_J: J5.10, MOO10.1
/M_OO_K: J5.11, MOO11.1
/M_OO_L: J5.12, MOO12.1
/M_OO_M: J5.13, MOO13.1
/M_OO_N: J5.14, MOO14.1
/M_OO_O: J5.15, MOO15.1
/M_OO_P: J5.16, MOO16.1
/M_OO_Q: J5.17, MOO17.1
/M_OO_R: J5.18, MOO18.1
/M_OO_S: J5.19, MOO19.1
/M_OO_T: J5.20, MOO20.1
/M_OO_U: J5.21, MOO21.1
/M_OO_V: J5.22, MOO22.1
/M_OO_W: J5.23, MOO23.1
/M_OO_X: J5.24, MOO24.1
/M_OO_Y: J5.25, MOO25.1
/M_OO_Z: J5.26, MOO26.1
/M_RI_A: J8.1, MRI1.1
/M_RI_B: J8.2, MRI2.1
/M_RI_C: J8.3, MRI3.1
/M_RI_D: J8.4, MRI4.1
/M_RI_E: J8.5, MRI5.1
/M_RI_F: J8.6, MRI6.1
/M_RI_G: J8.7, MRI7.1
/M_RI_H: J8.8, MRI8.1
/M_RI_I: J8.9, MRI9.1
/M_RI_J: J8.10, MRI10.1
/M_RI_K: J8.11, MRI11.1
/M_RI_L: J8.12, MRI12.1
/M_RI_M: J8.13, MRI13.1
/M_RI_N: J8.14, MRI14.1
/M_RI_O: J8.15, MRI15.1
/M_RI_P: J8.16, MRI16.1
/M_RI_Q: J8.17, MRI17.1
/M_RI_R: J8.18, MRI18.1
/M_RI_S: J8.19, MRI19.1
/M_RI_T: J8.20, MRI20.1
/M_RI_U: J8.21, MRI21.1
/M_RI_V: J8.22, MRI22.1
/M_RI_W: J8.23, MRI23.1
/M_RI_X: J8.24, MRI24.1
/M_RI_Y: J8.25, MRI25.1
/M_RI_Z: J8.26, MRI26.1
/M_RO_A: J6.1, MRO1.1
/M_RO_B: J6.2, MRO2.1
/M_RO_C: J6.3, MRO3.1
/M_RO_D: J6.4, MRO4.1
/M_RO_E: J6.5, MRO5.1
/M_RO_F: J6.6, MRO6.1
/M_RO_G: J6.7, MRO7.1
/M_RO_H: J6.8, MRO8.1
/M_RO_I: J6.9, MRO9.1
/M_RO_J: J6.10, MRO10.1
/M_RO_K: J6.11, MRO11.1
/M_RO_L: J6.12, MRO12.1
/M_RO_M: J6.13, MRO13.1
/M_RO_N: J6.14, MRO14.1
/M_RO_O: J6.15, MRO15.1
/M_RO_P: J6.16, MRO16.1
/M_RO_Q: J6.17, MRO17.1
/M_RO_R: J6.18, MRO18.1
/M_RO_S: J6.19, MRO19.1
/M_RO_T: J6.20, MRO20.1
/M_RO_U: J6.21, MRO21.1
/M_RO_V: J6.22, MRO22.1
/M_RO_W: J6.23, MRO23.1
/M_RO_X: J6.24, MRO24.1
/M_RO_Y: J6.25, MRO25.1
/M_RO_Z: J6.26, MRO26.1
/R_OI_A: J11.1, ROI1.1
/R_OI_B: J11.2, ROI2.1
/R_OI_C: J11.3, ROI3.1
/R_OI_D: J11.4, ROI4.1
/R_OI_E: J11.5, ROI5.1
/R_OI_F: J11.6, ROI6.1
/R_OI_G: J11.7, ROI7.1
/R_OI_H: J11.8, ROI8.1
/R_OI_I: J11.9, ROI9.1
/R_OI_J: J11.10, ROI10.1
/R_OI_K: J11.11, ROI11.1
/R_OI_L: J11.12, ROI12.1
/R_OI_M: J11.13, ROI13.1
/R_OI_N: J11.14, ROI14.1
/R_OI_O: J11.15, ROI15.1
/R_OI_P: J11.16, ROI16.1
/R_OI_Q: J11.17, ROI17.1
/R_OI_R: J11.18, ROI18.1
/R_OI_S: J11.19, ROI19.1
/R_OI_T: J11.20, ROI20.1
/R_OI_U: J11.21, ROI21.1
/R_OI_V: J11.22, ROI22.1
/R_OI_W: J11.23, ROI23.1
/R_OI_X: J11.24, ROI24.1
/R_OI_Y: J11.25, ROI25.1
/R_OI_Z: J11.26, ROI26.1
/R_OO_A: J9.1, ROO1.1
/R_OO_B: J9.2, ROO2.1
/R_OO_C: J9.3, ROO3.1
/R_OO_D: J9.4, ROO4.1
/R_OO_E: J9.5, ROO5.1
/R_OO_F: J9.6, ROO6.1
/R_OO_G: J9.7, ROO7.1
/R_OO_H: J9.8, ROO8.1
/R_OO_I: J9.9, ROO9.1
/R_OO_J: J9.10, ROO10.1
/R_OO_K: J9.11, ROO11.1
/R_OO_L: J9.12, ROO12.1
/R_OO_M: J9.13, ROO13.1
/R_OO_N: J9.14, ROO14.1
/R_OO_O: J9.15, ROO15.1
/R_OO_P: J9.16, ROO16.1
/R_OO_Q: J9.17, ROO17.1
/R_OO_R: J9.18, ROO18.1
/R_OO_S: J9.19, ROO19.1
/R_OO_T: J9.20, ROO20.1
/R_OO_U: J9.21, ROO21.1
/R_OO_V: J9.22, ROO22.1
/R_OO_W: J9.23, ROO23.1
/R_OO_X: J9.24, ROO24.1
/R_OO_Y: J9.25, ROO25.1
/R_OO_Z: J9.26, ROO26.1
/R_RI_A: J12.1, RRI1.1
/R_RI_B: J12.2, RRI2.1
/R_RI_C: J12.3, RRI3.1
/R_RI_D: J12.4, RRI4.1
/R_RI_E: J12.5, RRI5.1
/R_RI_F: J12.6, RRI6.1
/R_RI_G: J12.7, RRI7.1
/R_RI_H: J12.8, RRI8.1
/R_RI_I: J12.9, RRI9.1
/R_RI_J: J12.10, RRI10.1
/R_RI_K: J12.11, RRI11.1
/R_RI_L: J12.12, RRI12.1
/R_RI_M: J12.13, RRI13.1
/R_RI_N: J12.14, RRI14.1
/R_RI_O: J12.15, RRI15.1
/R_RI_P: J12.16, RRI16.1
/R_RI_Q: J12.17, RRI17.1
/R_RI_R: J12.18, RRI18.1
/R_RI_S: J12.19, RRI19.1
/R_RI_T: J12.20, RRI20.1
/R_RI_U: J12.21, RRI21.1
/R_RI_V: J12.22, RRI22.1
/R_RI_W: J12.23, RRI23.1
/R_RI_X: J12.24, RRI24.1
/R_RI_Y: J12.25, RRI25.1
/R_RI_Z: J12.26, RRI26.1
/R_RO_A: J10.1, RRO1.1
/R_RO_B: J10.2, RRO2.1
/R_RO_C: J10.3, RRO3.1
/R_RO_D: J10.4, RRO4.1
/R_RO_E: J10.5, RRO5.1
/R_RO_F: J10.6, RRO6.1
/R_RO_G: J10.7, RRO7.1
/R_RO_H: J10.8, RRO8.1
/R_RO_I: J10.9, RRO9.1
/R_RO_J: J10.10, RRO10.1
/R_RO_K: J10.11, RRO11.1
/R_RO_L: J10.12, RRO12.1
/R_RO_M: J10.13, RRO13.1
/R_RO_N: J10.14, RRO14.1
/R_RO_O: J10.15, RRO15.1
/R_RO_P: J10.16, RRO16.1
/R_RO_Q: J10.17, RRO17.1
/R_RO_R: J10.18, RRO18.1
/R_RO_S: J10.19, RRO19.1
/R_RO_T: J10.20, RRO20.1
/R_RO_U: J10.21, RRO21.1
/R_RO_V: J10.22, RRO22.1
/R_RO_W: J10.23, RRO23.1
/R_RO_X: J10.24, RRO24.1
/R_RO_Y: J10.25, RRO25.1
/R_RO_Z: J10.26, RRO26.1

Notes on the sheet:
BAY L (rotor slot W_L, D-sub J1..J4 = W.J1..J4)
BAY M (rotor slot W_M, D-sub J5..J8 = W.J1..J4)
BAY R (rotor slot W_R, D-sub J9..J12 = W.J1..J4)
ROTOR SOCKET (one per unit). The bay + the cartridge in it = one W card of the card arrangement: outbound: lead into J(4b+3) pin i+1 -> pin <b>OI(i+1) -> cartridge -> pin <b>OO(W[i]+1) -> J(4b+1) -> lead return: lead into J(4b+4) pin j+1 -> pin <b>RI(j+1) -> cartridge -> pin <b>RO(Winv[j]+1) -> J(4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

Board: 4 copper layers, 344 parts (16 on the bottom side), 320 nets, no tracks yet.

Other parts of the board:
LDW3: NPTH 3; NPTH_3mm
LDW4: NPTH 4; NPTH_4mm
MDW3: NPTH 3; NPTH_3mm
MDW4: NPTH 4; NPTH_4mm
RDW3: NPTH 3; NPTH_3mm
RDW4: NPTH 4; NPTH_4mm
